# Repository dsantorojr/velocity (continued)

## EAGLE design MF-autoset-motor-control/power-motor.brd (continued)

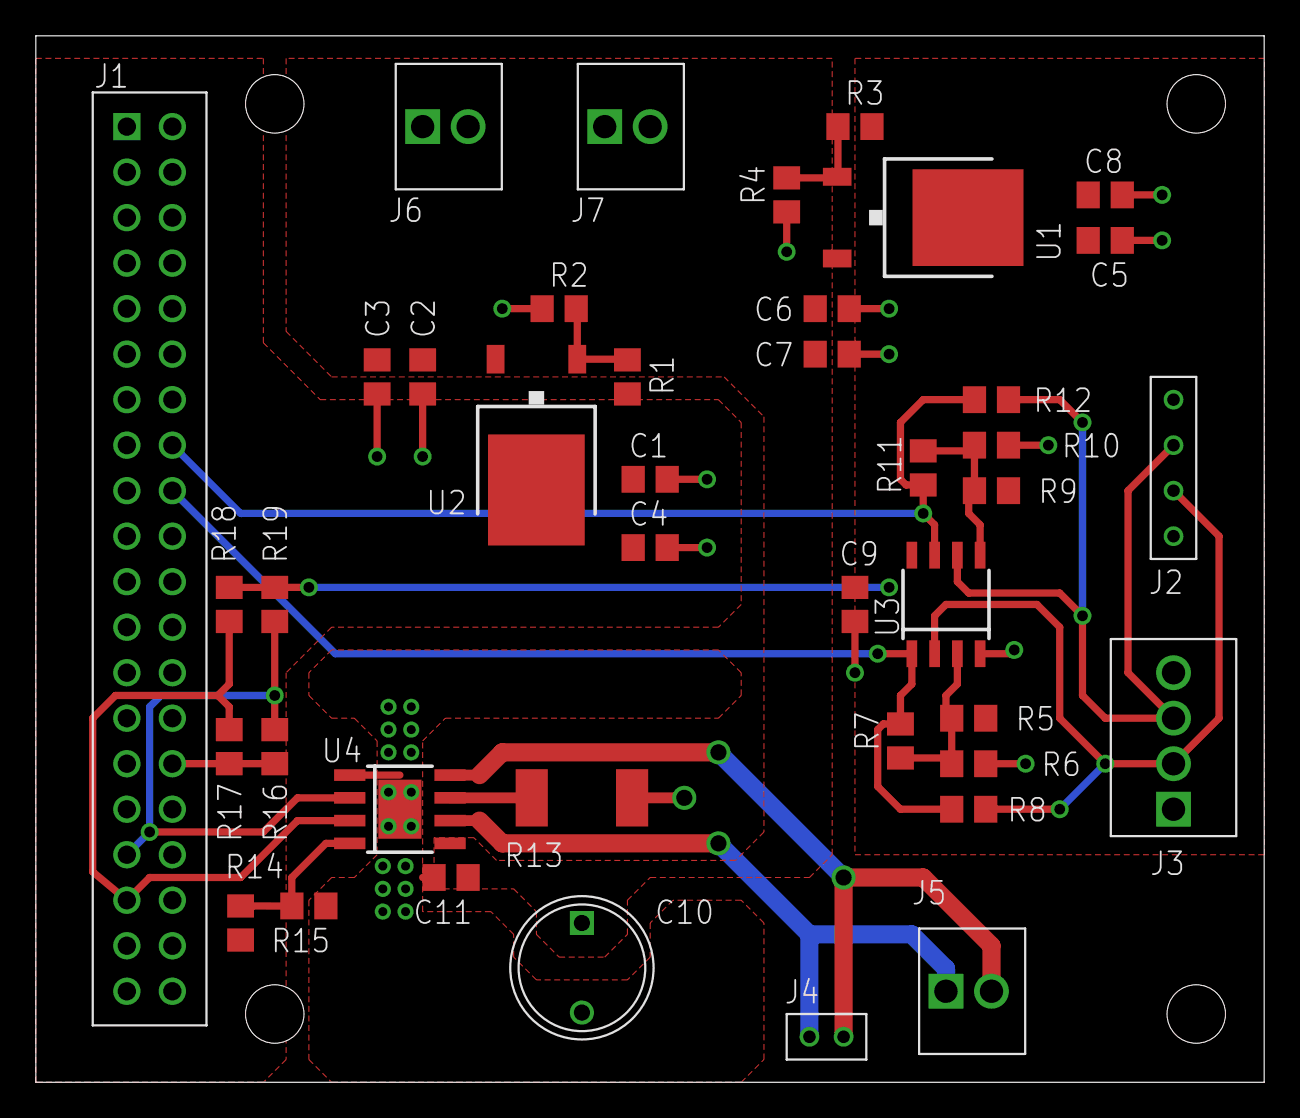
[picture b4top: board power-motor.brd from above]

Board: 2 copper layers, 68.6 x 58.4 mm, 41 parts (0 on the bottom side), 18 nets.

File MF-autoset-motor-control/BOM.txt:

Partlist exported from /Users/danielsantoro/Documents/eagle/velocity/power-motor/power-motor.sch at 9/14/16 1:04 AM

Qty Value              Device             Package         Parts                     Description DKPN            
2   0                  R0805              R0805           R8, R12                               311-0.0ARCT-ND X 
5   0.1u               C0805              C0805           C3, C4, C7, C8, C9                    1276-6468-1-ND X 
1   0.22u              C0805              C0805           C11                                   1276-1093-1-ND X
6   100k               R0805              R0805           R5, R6, R9, R10, R14, R15             311-100KCRCT-ND X
1   100u               C-POL8             CPOL-8          C10                                   1189-1860-ND X  
4   10k                R0805              R0805           R16, R17, R18, R19                    311-10.0KCRCT-ND X
4   10u                C0805              C0805           C1, C2, C5, C6                        490-5523-1-ND X   
2   121                R0805              R0805           R1, R3                                311-121CRCT-ND X 
1   200                R0805              R0805           R4                                    311-200ARCT-ND X
1   200                R2512              R2512           R13                                   541-200RCT-ND X 
1   365                R0805              R0805           R2                                    311-365CRCT-ND X  
2   576k               R0805              R0805           R7, R11                               311-576KCRCT-ND X
1   A4953ELJ           A4953ELJ           SOIC8           U4                                    620-1428-1-ND X
1   L293DT             L293DT             SOIC8           U3                                    497-8079-1-ND X
2   LD1085CDT-R        LD1085CDT-R        TO252           U1, U2                                497-3418-1-ND X 
1   RECT_2X20A         RECT_2X20A         RECT_2X20_0.1   J1                                    S9200-ND X     
3   TERM_1X2_0.1       TERM_1X2_0.1       TERM_1X2_0.1    J5, J6, J7                            ED10561-ND X     
1   TERM_1X4_0.1       TERM_1X4_0.1       TERM_1X4_0.1    J3                                    ED10563-ND X    
1   WIRE2BOARD_1X2     WIRE2BOARD_1X2     WIRE2BOARD_1X2  J4                                                    
1   WIRE2BOARD_1X4WIDE WIRE2BOARD_1X4WIDE WIRE2BOARD_1X4W J2

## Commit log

2016-12-03 first github commit
2016-12-06 Bord updates to go to 4 layers
2016-12-10 Multiple updates
    Library update (add switch)
    Updated sensing board to 4 layers, added some filtering.
    Updated control board to 4 layers, added functionality.
2016-12-12 Updates
    Sensing manufacture. Updated library. Updated main schematic to include
    magnetic sensor.
2016-12-13 Main Board Updates
    Move things away from holes. Create mfg files
2017-01-04 Supporting document and manufacturing update
2017-01-25 Google Drive Fix
2017-02-26 New layout for sensor board
